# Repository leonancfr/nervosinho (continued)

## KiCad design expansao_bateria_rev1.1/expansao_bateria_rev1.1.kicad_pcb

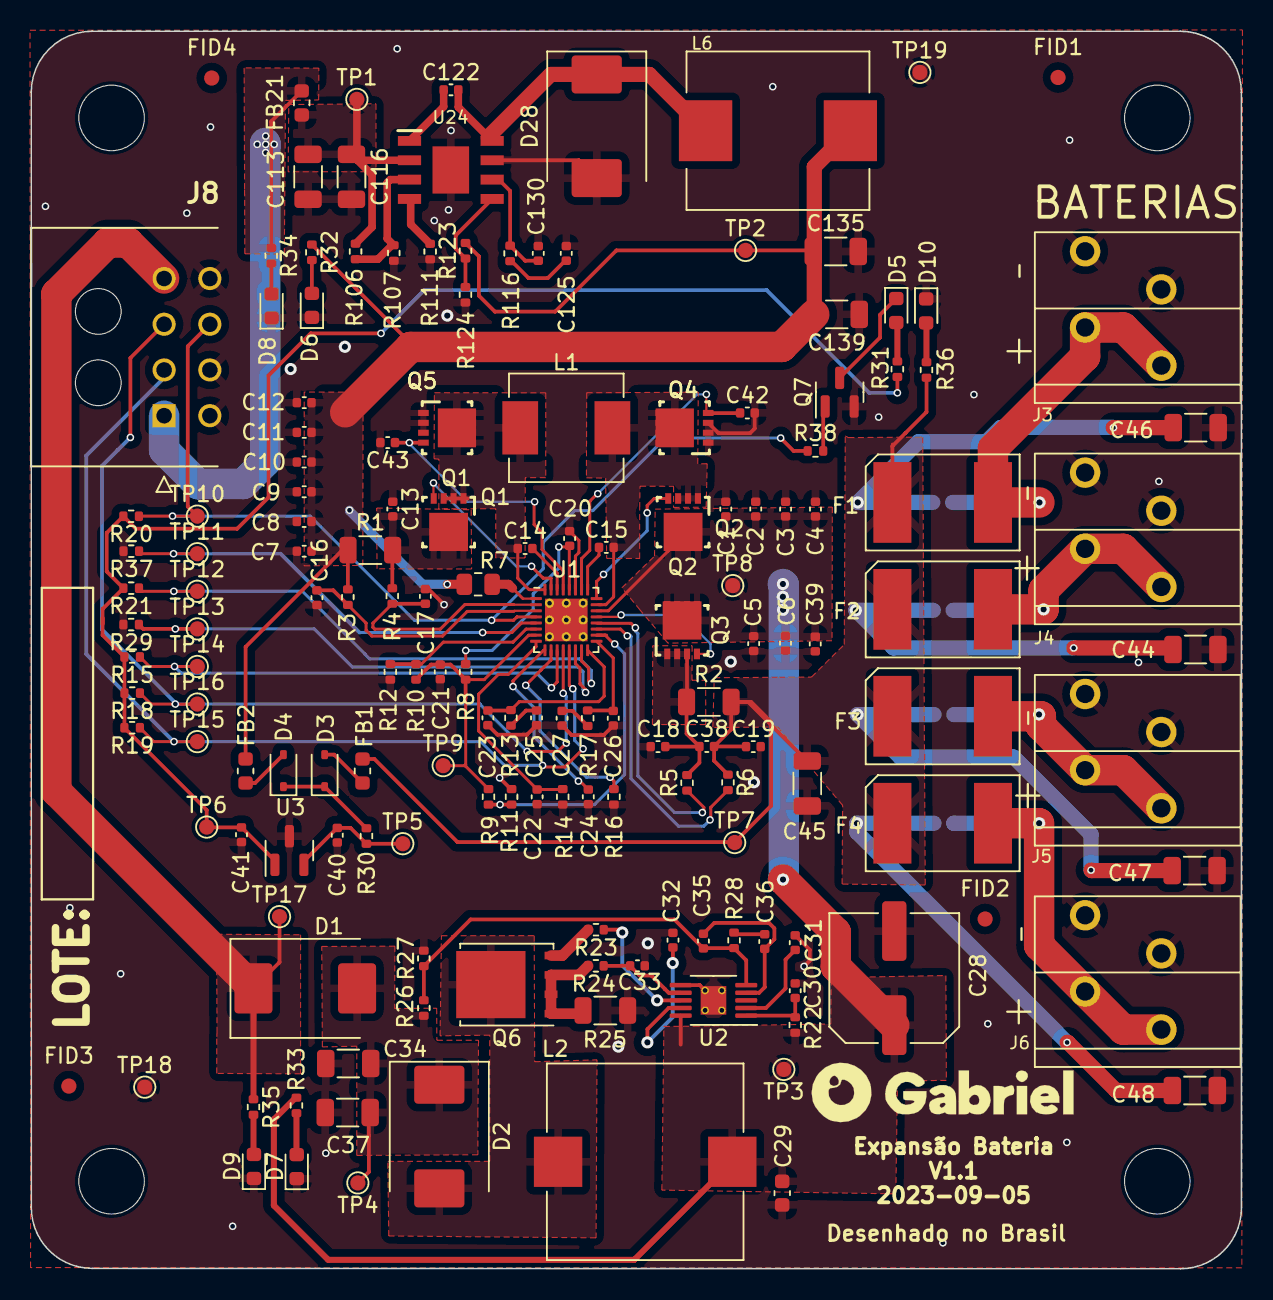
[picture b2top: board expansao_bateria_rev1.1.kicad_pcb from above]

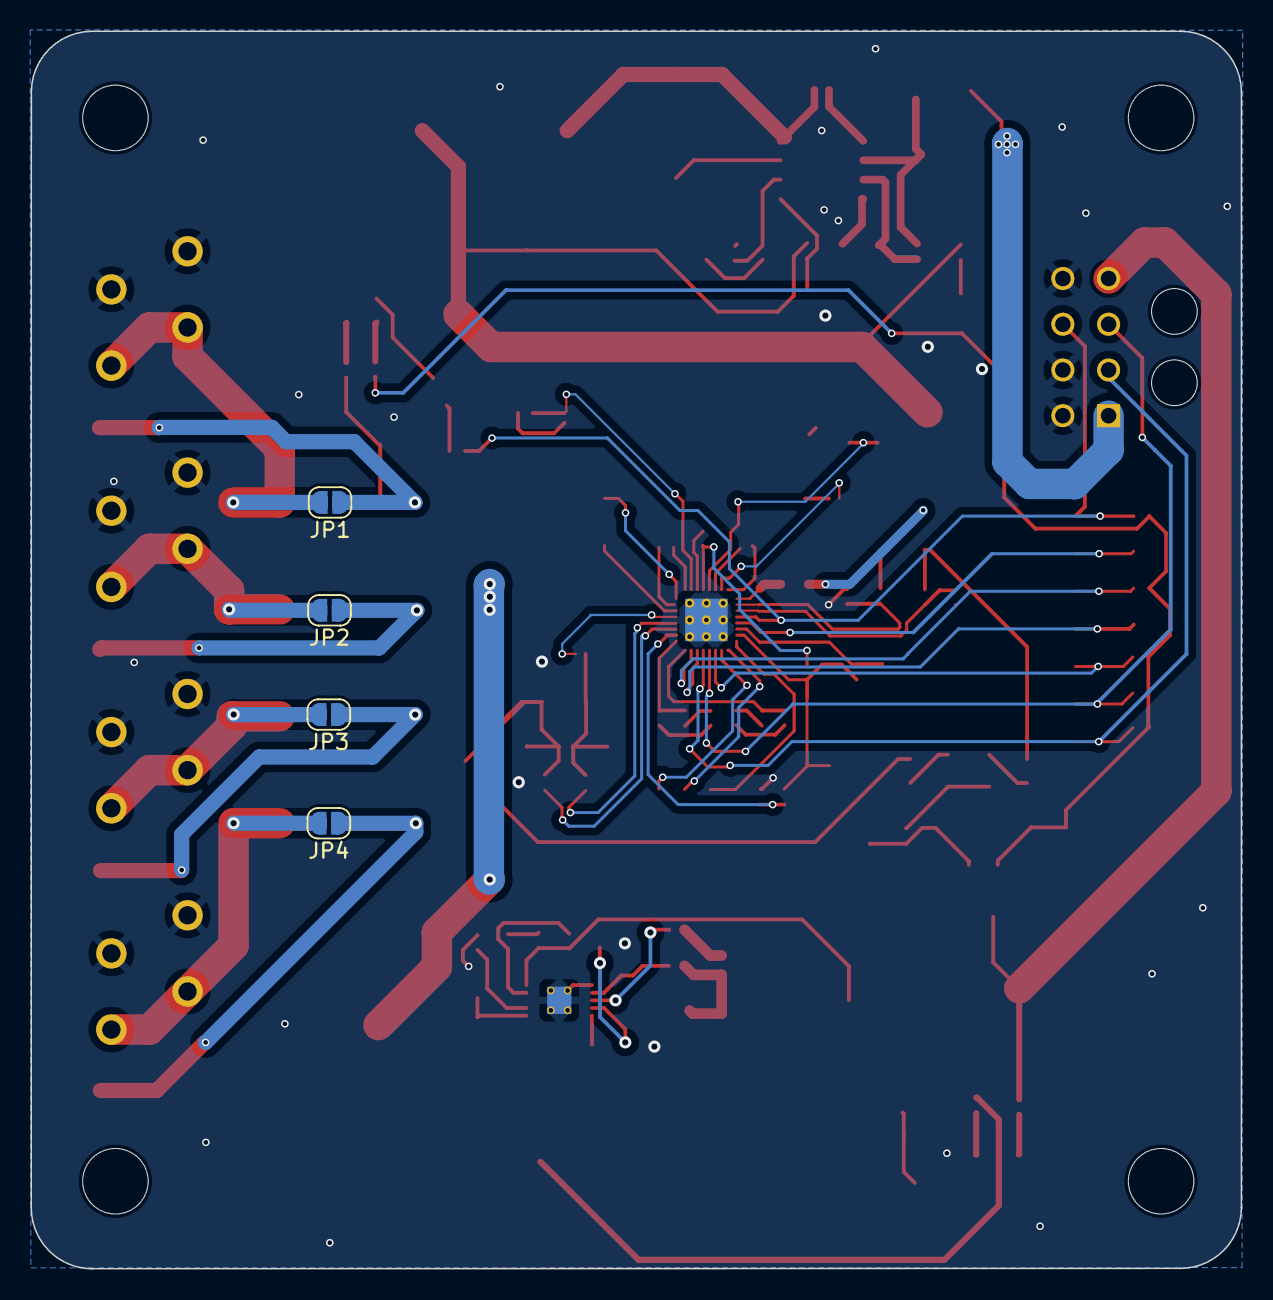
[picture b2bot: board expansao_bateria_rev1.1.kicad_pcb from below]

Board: 2 copper layers, 79.4 x 81.2 mm, 167 parts (4 on the bottom side), 77 nets.

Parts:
C1, C2, C3, C4, C5, C6, C7, C8, C9, C10, C11, C12, C13, C39: 4.7uF/25V; C_0402_1005Metric
C14, C15: 47nF/25V; C_0402_1005Metric
C16, C17, C18, C19: 33nF/25V; C_0402_1005Metric
C20: 2.2uF/16V; C_0402_1005Metric
C21: 1uF/25V; C_0402_1005Metric
C22, C24: 100pF; C_0402_1005Metric
C23: 33pF; C_0402_1005Metric
C25: 1800pF; C_0402_1005Metric
C26: 15pF; C_0402_1005Metric
C27: 680pF; C_0402_1005Metric
C28: 56uF/25V; C_Elec_8x5.4
C29: 470nF/25V; C_0603_1608Metric
C30: 100pF/50V; C_0402_1005Metric
C31: 68nF/10V; C_0402_1005Metric
C32: 1uF/16V; C_0402_1005Metric
C33: 470pF/50V; C_0402_1005Metric
C34, C37, C113, C116: 2.2uF/100V; C_1206_3216Metric
C35: 680pF/50V; C_0402_1005Metric
C36: 22nF/50V; C_0402_1005Metric
C38, C40, C41: 0.1uF/25V; C_0402_1005Metric
C42, C43: 150PF/25V; C_0402_1005Metric
C44, C45, C47, C48: 4.7uF/25V; C_1206_3216Metric
C46: 10uF/25V; C_1206_3216Metric
C122: 100nF/100V; C_0402_1005Metric
C125: 6.8nF/50V; C_0402_1005Metric
C130: 39pF/50V; C_0402_1005Metric
C135, C139: 47uF/16V; C_1206_3216Metric
D1: ACDBC560; D_SMC
D2: B370-13-F; D_SMC
D3, D4: BAT54HT1G; D_SOD-323
D5, D6, D7, D8, D9, D10: LED; LED_0603_1608Metric
D28: B560C; D_SMC
F1, F2, F3, F4: BSMD2920-600-16V; BSMD2920
FB1, FB2, FB21: FerriteBead_Small; L_0603_1608Metric
FID1, FID2, FID3, FID4: Fiducial; Fiducial_1mm_Mask2mm
J3, J4, J5, J6: Conn_01x02; KF202-5.0-2P
J8: 43045-0800; 43045-08_00,01,02,10_
JP1, JP2, JP3, JP4: SolderJumper-2_P1.3mm_Open_RoundedPad1.0x1.5mm
L1: 2.2uH / 9.5A; L_Sunlord_MWSA0603S
L2: IHLP5050CEER2R2M01; L_Vishay_IHLP-5050
L6: 8.2uH; MHCC10040-8R2M-R7
MK1, MK2, MK3, MK4: Mounting_Hole; MountingHole_4.3mm_M4
Q1, Q2, Q4, Q5: CSD17551Q3A; DNH0008A
Q3: CSD25402Q3A; DNH0008A
Q6: NTMFS5C673NLT1G; TDSON-8-1
Q7: PJM2302NSA-S; SOT-23
R1, R2: 10m; R_1206_3216Metric
R3, R4: 4.99; R_0402_1005Metric
R5, R6, R8, R30: 10 Ohm; R_0402_1005Metric
R7: 1 ohm; R_0805_2012Metric
R9: 39k; R_0402_1005Metric
R10: 383k; R_0402_1005Metric
R11: 100k; R_0402_1005Metric
R12: 220k; R_0402_1005Metric
R13: 40.2k; R_0402_1005Metric
R14: 137k; R_0402_1005Metric
R15, R17, R18, R19, R20, R21, R29, R34, R35, R37: 10k; R_0402_1005Metric
R16: 30k; R_0402_1005Metric
R22: 681kOhm; R_0402_1005Metric
R23: 11.3 Ohm; R_0402_1005Metric
R24: 2.61 ohm; R_0402_1005Metric
R25: 4m Ohm; R_1206_3216Metric
R26: 56k; R_0402_1005Metric
R27: 825 Ohm; R_0402_1005Metric
R28: 18.7kOhm; R_0402_1005Metric
R31, R32, R33, R36: 2k2; R_0402_1005Metric
R38: 180R; R_0402_1005Metric
R106: 523k; R_0402_1005Metric
R107: 84k5; R_0402_1005Metric
R111: 162k; R_0402_1005Metric
R116: 13k; R_0402_1005Metric
R123: 60k4; R_0402_1005Metric
R124: 4k3; R_0402_1005Metric
TP1, TP2, TP3, TP4, TP5, TP6, TP7, TP8, TP9, TP17: TestPoint; TestPoint_Pad_D1.0mm
TP10, TP11, TP12, TP13, TP14, TP15, TP16, TP18, TP19: TestPoint_Pad_D1.0mm
U1: BQ25713RSNR; Texas_S-PWQFN-N32_EP2.8x2.8mm_ThermalVias
U2: TPS40210DGQ; MSOP-10-1EP_3x3mm_P0.5mm_EP1.68x1.88mm_ThermalVias
U3: LM3480-3.3; SOT-23
U24: TPS54360BDDAR; SOIC127P600X170-9N

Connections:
/+3V3_BMS: C41.1, R15.2, R18.2, R19.2, R20.2, R21.2, R31.1, TP6.1, U3.1 (VO)
/+12V_INPUT_BMS: C7.1, C8.1, C9.1, C10.1, C11.1, C12.1, C135.1, C139.2, FB2.1, L6.2, R1.1, R3.1, R7.1, R32.1, R123.2, TP2.1
/+12V_OUTPUT_BMS: C1.1, C2.1, C3.1, C4.1, C5.1, C6.1, C28.1, C29.1, C39.1, L2.1, Q2.5 (D), Q2.6 (D), Q2.7 (D), Q2.8 (D), Q2.9 (D), Q3.5 (S), Q3.6 (S), Q3.7 (S), Q3.8 (S), Q3.9 (S), R22.1, R33.1, TP3.1, TP8.1, U1.22 (SYS), U2.10 (VDD)
/+48V_FROM_SYSTEM: FB21.1, J8.1, R34.1
/+48V_TO_SYSTEM: D1.1 (K), J8.4, R35.1, TP17.1
/BATTERY1+: F1.2, J3.1, JP1.2 (B)
/BATTERY2+: F2.2, J4.1, JP2.2 (B)
/BATTERY3+: F3.2, J5.1, JP3.2 (B)
/BATTERY4+: F4.2, J6.1, JP4.2 (B)
/BATTERY_CONN+: C19.1, C38.2, C44.1, C45.1, C46.2, C47.1, C48.1, F1.1, F2.1, F3.1, F4.1, FB1.1, JP1.1 (A), JP2.1 (A), JP3.1 (A), JP4.1 (A), R2.2, R6.1, R36.1, TP7.1
/CHRG_OK_BMS: J8.7, R20.1, R38.1, TP10.1, U1.4 (CHRG_OK)
/CMPIN_BMS: R29.1, TP13.1, U1.14 (CMPIN)
/CMPOUT_BMS: R21.1, TP12.1, U1.15 (CMPOUT)
/EN_OTG_BMS: R37.1, TP11.1, U1.5 (EN_OTG)
/PROCHOT_BMS: R15.1, TP14.1, U1.11 (PROCHOT)
/Power Management/OUTPUT_+48V: C34.2, C37.2, D1.2 (A), D2.1 (K), R26.1, TP4.1
/SCL_BMS: J8.2, R19.1, TP15.1, U1.13 (SCL)
/SDA_BMS: J8.3, R18.1, TP16.1, U1.12 (SDA)
/battery_manager/CSIN+: C16.1, R3.2, U1.3 (ACP)
/battery_manager/CSIN-: C17.1, R4.1, U1.2 (ACN)
/battery_manager/CSOUT+: R5.1, U1.20 (SRP)
/battery_manager/CSOUT-: R6.2, U1.19 (SRN)
/battery_manager/REGN: C20.1, R8.1, U1.28 (REGN)
/battery_manager/VDDA: C21.1, R8.2, R9.1, R10.2, TP9.1, U1.7 (VDDA)
GND: C1.2, C2.2, C3.2, C4.2, C5.2, C6.2, C7.2, C8.2, C9.2, C10.2, C11.2, C12.2, C13.1, C16.2, C17.2, C18.2, C19.2, C20.2, C21.2, C22.2, C23.2, C24.2, C25.2, C26.2, C27.2, C28.2, C29.2, C30.2, C31.1, C32.1, C33.2, C34.1, C37.1, C39.2, C40.2, C41.2, C42.2, C43.2, C44.2, C45.2, C46.1, C47.2, C48.2, C113.1, C116.2, C125.1, C130.2, C135.2, C139.1, D6.1 (K), D7.1 (K), D8.1 (K), D9.1 (K), D10.1 (K), D28.2 (A), J3.2, J4.2, J5.2, J6.2, J8.5, J8.6, J8.8, Q4.1 (S), Q4.2 (S), Q4.3 (S), Q5.1 (S), Q5.2 (S), Q5.3 (S), Q7.2 (S), R11.2, R12.1, R14.2, R16.2, R25.2, R27.2, R29.2, R37.2, R107.2, R111.1, R124.2, TP18.1, TP19.1, U1.27 (GND), U1.33 (PWPAD), U2.6 (GND), U2.11 (PWPD), U3.3 (GND), U24.7 (GND), U24.9 (PAD)
unnamed: C13.2, Q1.5 (D), Q1.6 (D), Q1.7 (D), Q1.8 (D), Q1.9 (D), R1.2, R4.2
unnamed: C18.1, C38.1, Q3.1 (D), Q3.2 (D), Q3.3 (D), R2.1, R5.2
unnamed: C25.1, R13.1
unnamed: C27.1, R17.1
unnamed: C36.1, R28.2
unnamed: C125.2, R116.2
unnamed: D2.2 (A), L2.2, Q6.5 (D)
unnamed: D3.2 (A), FB1.2
unnamed: D3.1 (K), D4.1 (K), R30.1
unnamed: D4.2 (A), FB2.2
unnamed: D5.2 (A), R31.2
unnamed: D5.1 (K), Q7.3 (D)
unnamed: D6.2 (A), R32.2
unnamed: D7.2 (A), R33.2
unnamed: D8.2 (A), R34.2
unnamed: D9.2 (A), R35.2
unnamed: D10.2 (A), R36.2
unnamed: C122.2, D28.1 (K), L6.1, U24.8 (SW)
unnamed: Q1.4 (G), U1.31 (HIDRV1)
unnamed: Q2.4 (G), U1.24 (HIDRV2)
unnamed: Q3.4 (G), U1.21 (BATDRV)
unnamed: C42.1, Q4.4 (G), U1.26 (LODRV2)
unnamed: C43.1, Q5.4 (G), U1.29 (LODRV1)
unnamed: Q6.4 (G), R23.2
unnamed: Q6.1 (S), Q6.2 (S), Q6.3 (S), R24.2, R25.1
unnamed: Q7.1 (G), R38.2
unnamed: C14.2, U1.30 (BTST1)
unnamed: C15.1, U1.25 (BTST2)
unnamed: R9.2, R11.1, U1.18 (CELL_BATPRESZ)
unnamed: C23.1, R13.2, U1.16 (COMP1)
unnamed: C26.1, R17.2, U1.17 (COMP2)
unnamed: C22.1, R14.1, U1.8 (IADPT)
unnamed: C24.1, U1.9 (IBAT)
unnamed: R10.1, R12.2, U1.6 (ILIM_HIZ)
unnamed: R16.1, U1.10 (PSYS)
unnamed: C14.1, L1.1, Q1.1 (S), Q1.2 (S), Q1.3 (S), Q5.5 (D), Q5.6 (D), Q5.7 (D), Q5.8 (D), Q5.9 (D), U1.32 (SW1)
unnamed: C15.2, L1.2, Q2.1 (S), Q2.2 (S), Q2.3 (S), Q4.5 (D), Q4.6 (D), Q4.7 (D), Q4.8 (D), Q4.9 (D), U1.23 (SW2)
unnamed: R7.2, U1.1 (VBUS)
unnamed: C32.2, U2.9 (BP)
unnamed: C35.2, C36.2, U2.4 (COMP)
unnamed: C35.1, R26.2, R27.1, R28.1, U2.5 (FB)
unnamed: R23.1, U2.8 (GDRV)
unnamed: C33.1, R24.1, U2.7 (ISNS)
unnamed: C30.1, R22.2, U2.1 (RC)
unnamed: C31.2, U2.2 (SS)
unnamed: C40.1, R30.2, TP5.1, U3.2 (VI)
unnamed: C122.1, U24.1 (BOOT)
unnamed: C130.1, R116.1, U24.6 (COMP)
unnamed: R106.2, R107.1, U24.3 (EN)
unnamed: R123.1, R124.1, U24.5 (FB)
unnamed: R111.2, U24.4 (RT/CLK)
unnamed: C113.2, C116.1, FB21.2, R106.1, TP1.1, U24.2 (VIN)

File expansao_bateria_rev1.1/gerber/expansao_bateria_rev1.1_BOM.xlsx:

expansao_bateria_rev1.0.0_BOM
Id | Designator | Quantity | Comment | Footprint | LCSC Part Number
1 | C1, C2, C3, C4, C5, C6, C7, C8, C9, C10, C11, C12, C13, C39 | 14 | 4.7uF/25V | Capacitor_SMD:C_0402_1005Metric | C318563
2 | C14, C15 | 2 | 47nF/25V | Capacitor_SMD:C_0402_1005Metric | C437528
3 | C16, C17, C18, C19 | 4 | 33nF/25V | Capacitor_SMD:C_0402_1005Metric | C185046
4 | C20 | 1 | 2.2uF/16V | Capacitor_SMD:C_0402_1005Metric | C170151
5 | C21 | 1 | 1uF/25V | Capacitor_SMD:C_0402_1005Metric | C466612
6 | C22, C24 | 2 | 100pF | Capacitor_SMD:C_0402_1005Metric | C696853
7 | C23 | 1 | 33pF | Capacitor_SMD:C_0402_1005Metric | C342945
8 | C25 | 1 | 1800pF | Capacitor_SMD:C_0402_1005Metric | C696873
9 | C26 | 1 | 15pF | Capacitor_SMD:C_0402_1005Metric | C1548
10 | C27 | 1 | 680pF | Capacitor_SMD:C_0402_1005Metric | C1541
11 | C28 | 1 | 56uF/25V | Capacitor_SMD:C_Elec_8x5.4 | C445041
12 | C29 | 1 | 470nF/25V | Capacitor_SMD:C_0603_1608Metric | C5448876
13 | C30 | 1 | 100pF/50V | Capacitor_SMD:C_0402_1005Metric | C696853
14 | C31 | 1 | 68nF/10V | Capacitor_SMD:C_0402_1005Metric | C541398
15 | C32 | 1 | 1uF/16V | Capacitor_SMD:C_0402_1005Metric | C466612
16 | C33 | 1 | 470pF/50V | Capacitor_SMD:C_0402_1005Metric | C1537
17 | C35 | 1 | 680pF/50V | Capacitor_SMD:C_0402_1005Metric | C1541
18 | C36 | 1 | 22nF/50V | Capacitor_SMD:C_0402_1005Metric | C5137627
19 | C34, C37, C113, C116 | 4 | 2.2uF/100V | Capacitor_SMD:C_1206_3216Metric | C170101
20 | C38, C40, C41 | 3 | 0.1uF/25V | Capacitor_SMD:C_0402_1005Metric | C6534351
21 | C42, C43 | 2 | 150PF/25V | Capacitor_SMD:C_0402_1005Metric | C541384
22 | C44, C45, C47, C48 | 4 | 4.7uF/25V | Capacitor_SMD:C_1206_3216Metric | C706802
23 | C46 | 1 | 10uF/25V | Capacitor_SMD:C_1206_3216Metric | C14860
24 | C122 | 1 | 100nF/100V | Capacitor_SMD:C_0402_1005Metric | C113803
25 | C125 | 1 | 6.8nF/50V | Capacitor_SMD:C_0402_1005Metric | C123518
26 | C130 | 1 | 39pF/50V | Capacitor_SMD:C_0402_1005Metric | C376784
27 | C135, C139 | 2 | 47uF/16V | Capacitor_SMD:C_1206_3216Metric | C172351
28 | D1 | 1 | ACDBC560 | Diode_SMD:D_SMC | C3019749
29 | D2 | 1 | B370-13-F | Diode_SMD:D_SMC | C134456
30 | D3, D4 | 2 | BAT54HT1G | Diode_SMD:D_SOD-323 | C12744
31 | D5, D6, D7, D8, D9, D10 | 6 | LED | LED_SMD:LED_0603_1608Metric | C84264
32 | D28 | 1 | B560C | Diode_SMD:D_SMC | C85100
33 | F1, F2, F3, F4 | 4 | BSMD2920-600-16V | Fuse:BSMD2920 | C910847
34 | FB1, FB2, FB21 | 3 | FerriteBead_Small | Inductor_SMD:L_0603_1608Metric | C394410
35 | J3, J4, J5, J6 | 4 | Conn_01x02 | Connector:KF202-5.0-2P | C475182
36 | J8 | 1 | 43045-0800 | Connector_Molex:43045-08_00,01,02,10_ | C437083
37 | L1 | 1 | 2.2uH / 9.5A | Inductor_SMD:L_Sunlord_MWSA0603S | C408445
38 | L2 | 1 | IHLP5050CEER2R2M01 | Inductor_SMD:L_Vishay_IHLP-5050 | C845090
39 | L6 | 1 | 8.2uH | Inductor_SMD:MHCC10040-8R2M-R7 | C285788
40 | Q1, Q2, Q4, Q5 | 4 | CSD17551Q3A | Package_SON:DNH0008A | C2876535
41 | Q3 | 1 | CSD25402Q3A | Package_SON:DNH0008A | C111356
42 | Q6 | 1 | NTMFS5C673NT1G | Package_TO_SOT_SMD:TDSON-8-1 | C604444
43 | Q7 | 1 | PJM2302NSA-S | Package_TO_SOT_SMD:SOT-23 | C411710
44 | R1, R2 | 2 | 10mOhm | Resistor_SMD:R_1206_3216Metric | C364375
45 | R3, R4 | 2 | 4.99 Ohm | Resistor_SMD:R_0402_1005Metric | C111356
46 | R5, R6, R8, R30 | 4 | 10 Ohm | Resistor_SMD:R_0402_1005Metric | C413044
47 | R7 | 1 | 1 ohm | Resistor_SMD:R_0805_2012Metric | C473606
48 | R9 | 1 | 39k | Resistor_SMD:R_0402_1005Metric | C911877
49 | R10 | 1 | 383k | Resistor_SMD:R_0402_1005Metric | C166572
50 | R11 | 1 | 100k | Resistor_SMD:R_0402_1005Metric | C60491
51 | R12 | 1 | 220k | Resistor_SMD:R_0402_1005Metric | C2909335
52 | R13 | 1 | 40.2k | Resistor_SMD:R_0402_1005Metric | C100415
53 | R14 | 1 | 137k | Resistor_SMD:R_0402_1005Metric | C5153963
54 | R15, R17, R18, R19, R20, R21, R29, R34, R35, R37 | 10 | 10k | Resistor_SMD:R_0402_1005Metric | C25531
55 | R16 | 1 | 30k | Resistor_SMD:R_0402_1005Metric | C2906928
56 | R22 | 1 | 681kOhm | Resistor_SMD:R_0402_1005Metric | C3015639
57 | R23 | 1 | 11.3 Ohm | Resistor_SMD:R_0402_1005Metric | C3445748
58 | R24 | 1 | 2.61 ohm | Resistor_SMD:R_0402_1005Metric | C321166
59 | R25 | 1 | 4m Ohm | Resistor_SMD:R_1206_3216Metric | C912755
60 | R26 | 1 | 56k | Resistor_SMD:R_0402_1005Metric | C163438
61 | R27 | 1 | 825 Ohm | Resistor_SMD:R_0402_1005Metric | C5126010
62 | R28 | 1 | 18.7kOhm | Resistor_SMD:R_0402_1005Metric | C11476
63 | R31, R32, R33, R36 | 4 | 2k2 | Resistor_SMD:R_0402_1005Metric | C2906920
64 | R106 | 1 | 523k | Resistor_SMD:R_0402_1005Metric | C23076
65 | R107 | 1 | 84k5 | Resistor_SMD:R_0402_1005Metric | C403376
66 | R111 | 1 | 162k | Resistor_SMD:R_0402_1005Metric | C403015
67 | R116 | 1 | 13k | Resistor_SMD:R_0402_1005Metric | C170711
68 | R123 | 1 | 60k4 | Resistor_SMD:R_0402_1005Metric | C403296
69 | R124 | 1 | 4k3 | Resistor_SMD:R_0402_1005Metric | C23159
70 | U1 | 1 | BQ25713RSNR | Package_DFN_QFN:Texas_S-PWQFN-N32_EP2.8x2.8mm_ThermalVias | C2878935
71 | U2 | 1 | TPS40210DGQ | Package_SO:MSOP-10-1EP_3x3mm_P0.5mm_EP1.68x1.88mm_ThermalVias | C14728
72 | U3 | 1 | LM3480-3.3 | Package_TO_SOT_SMD:SOT-23 | C5380665
73 | U24 | 1 | TPS54360BDDAR | Package_SO:SOIC127P600X170-9N | C524806

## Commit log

2024-02-10 initial commit - backup
